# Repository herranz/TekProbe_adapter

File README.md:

# TekProbe_adapter
An adapter specially created to adapt TekProbe BNC probes to oscilloscopes without that type of connection

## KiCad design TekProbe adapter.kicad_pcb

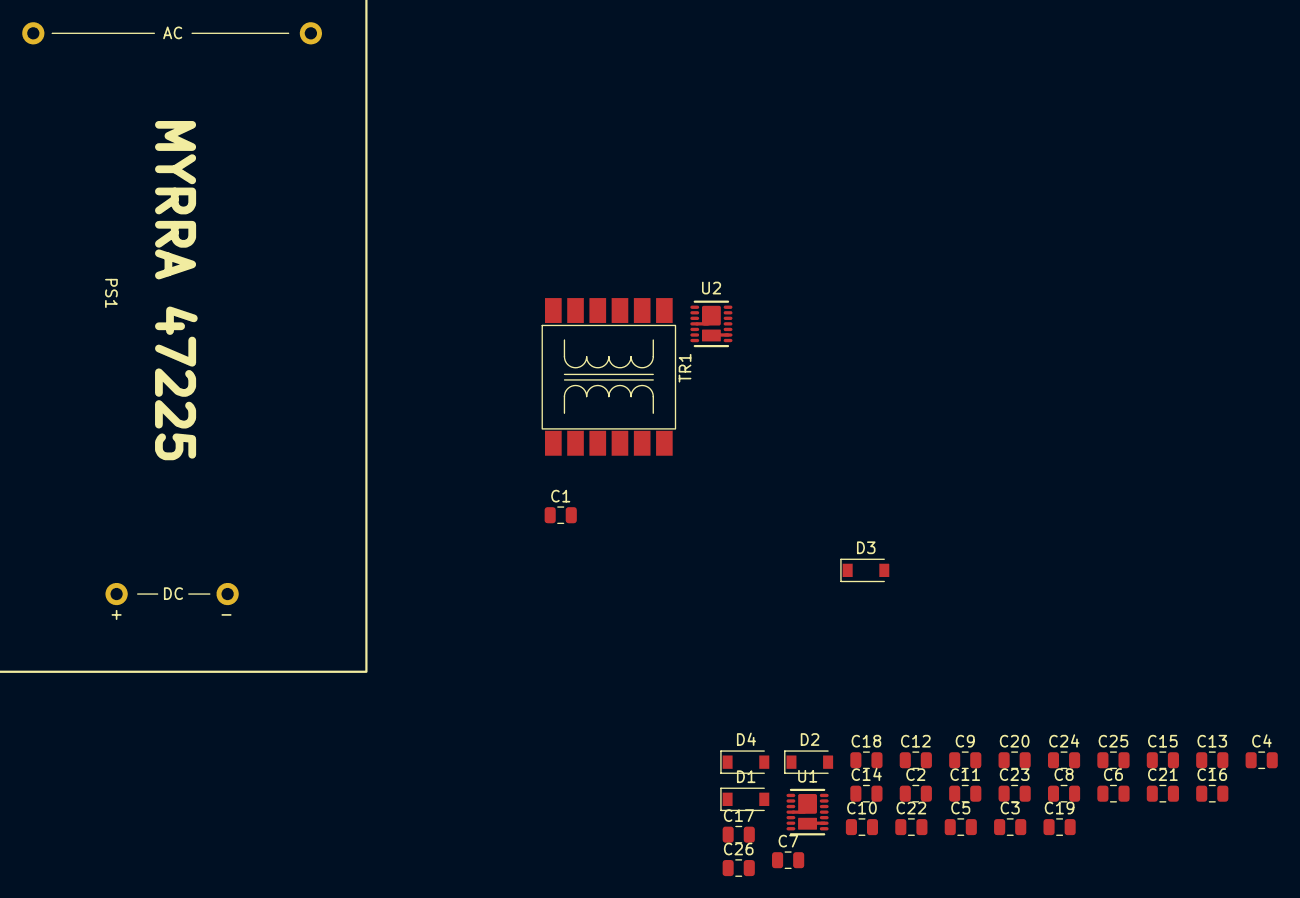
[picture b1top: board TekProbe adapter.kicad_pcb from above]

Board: 2 copper layers, 34 parts (0 on the bottom side), 22 nets, no tracks yet.

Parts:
C1, C2, C3, C4, C6, C7, C8, C9, C10, C23, C24, C25, C26: 10uF; C_0805_2012Metric
C5, C11, C12, C13, C14, C19, C20, C21, C22: 0.1uF; C_0805_2012Metric
C15, C16, C17, C18: 3300pF; C_0805_2012Metric
D1, D2, D3, D4: 1N4148W; D_SOD-123
PS1: Myrra_47225; MYRRA 47225
TR1: WE-flex_749196141_ALT; WE-FLEX 749196141
U1: LT3032-xDE-15; SON50P300X400X80-15N
U2: LT3032-xDE-5; SON50P300X400X80-15N

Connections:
+5V: C17.2, C19.1, C23.1, U2.1 (OUTP)
+7.5V: C7.1, C8.1, C12.1, C13.1, U1.6 (INN@1), U1.9 (INN@2), U1.10 (~SHDNN), U1.12 (~SHDNP), U1.14 (INP), U1.16 (INN@3)
+9V: C9.1, C14.1, U2.10 (~SHDNN), U2.12 (~SHDNP), U2.14 (INP)
+15V: C15.2, C21.1, C25.1, U1.1 (OUTP)
-5V: C18.2, C20.1, C24.1, U2.7 (OUTN)
-9V: C10.1, C11.1, U2.6 (INN@1), U2.9 (INN@2), U2.16 (INN@3)
-15V: C16.2, C22.1, C26.1, U1.7 (OUTN)
GND: C2.2, C3.1, C7.2, C8.2, C9.2, C10.2, C11.2, C12.2, C13.2, C14.2, C19.2, C20.2, C21.2, C22.2, C23.2, C24.2, C25.2, C26.2, TR1.8, TR1.12, U1.4 (GND), U1.5 (GND), U1.15 (GND), U2.4 (GND), U2.5 (GND), U2.15 (GND)
GND1: C5.2, C6.2, PS1.3 (-Vout), TR1.5, TR1.6
unnamed: C1.1, D1.1 (K)
unnamed: C1.2, C2.1, D2.1 (K)
unnamed: C3.2, C4.1, D3.2 (A)
unnamed: C4.2, D4.2 (A)
unnamed: C15.1, U1.3 (BYPP)
unnamed: C16.1, U1.11 (BYPN)
unnamed: C17.1, U2.3 (BYPP)
unnamed: C18.1, U2.11 (BYPN)
unnamed: D1.2 (A), TR1.1
unnamed: D2.2 (A), TR1.4, TR1.11
unnamed: D3.1 (K), TR1.9, TR1.10
unnamed: D4.1 (K), TR1.7
VDD: C5.1, C6.1, PS1.4 (+Vout), TR1.2, TR1.3

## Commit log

2022-09-18 Commit inicial
